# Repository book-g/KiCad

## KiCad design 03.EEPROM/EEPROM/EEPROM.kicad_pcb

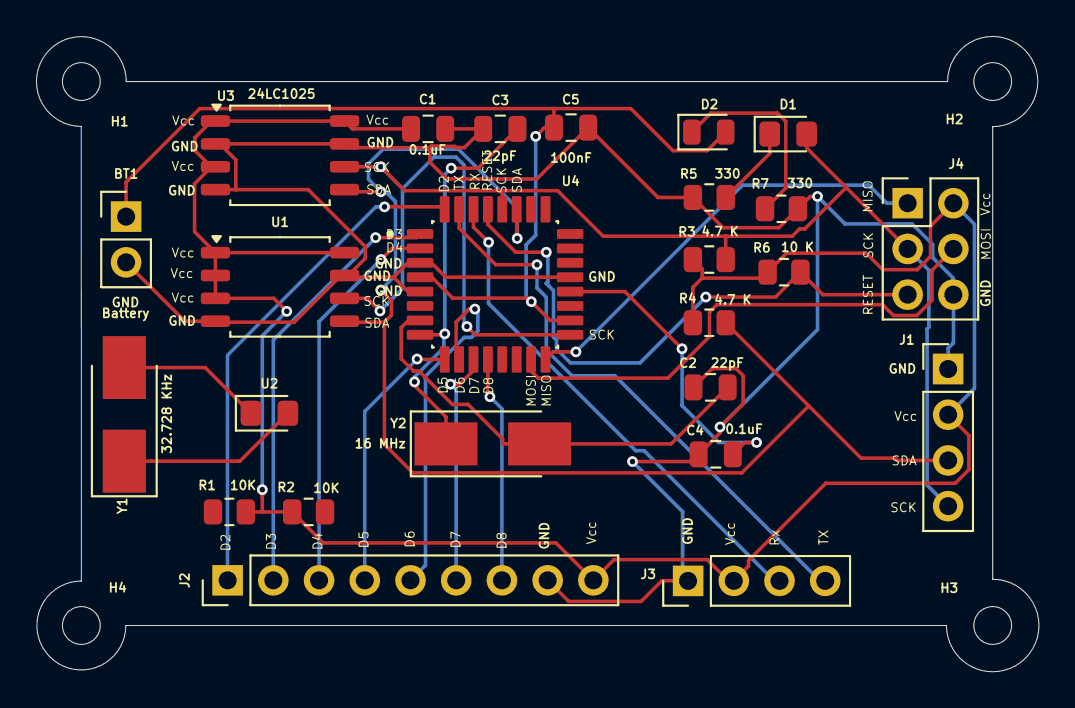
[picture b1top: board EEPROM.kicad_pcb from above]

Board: 2 copper layers, 55.7 x 35.3 mm, 29 parts (0 on the bottom side), 24 nets.

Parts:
BT1: Battery; PinHeader_1x02_P2.54mm_Vertical
C1, C4: 0.1uF; C_0805_2012Metric
C2, C3: 22pF; C_0805_2012Metric
C5: 100nF; C_0805_2012Metric
D1: LED; LED_0805_2012Metric_Pad1.15x1.40mm_HandSolder
D2: LED; LED_0805_2012Metric
H1, H2, H3, H4: MountingHole; MountingHole_2.1mm
J1, J3: Conn_01x04_Pin; PinHeader_1x04_P2.54mm_Vertical
J2: Conn_01x09_Pin; PinHeader_1x09_P2.54mm_Vertical
J4: Conn_02x03_Odd_Even; PinHeader_2x03_P2.54mm_Vertical
R1, R2: 10K; R_0805_2012Metric
R3, R4: 4.7 K; R_0805_2012Metric
R5, R7: 330; R_0805_2012Metric
R6: 10 K; R_0805_2012Metric
U1, U3: 24LC1025; SOIC-8_5.3x5.3mm_P1.27mm
U2: DS1337S_; LED_0805_2012Metric_Pad1.15x1.40mm_HandSolder
U4: ATMEGA328P-AU; QFP80P900X900X120-32N
Y1: 32.728 KHz; Crystal_SMD_5032-2Pin_5.0x3.2mm_HandSoldering
Y2: 16 MHz; Crystal_SMD_5032-2Pin_5.0x3.2mm_HandSoldering

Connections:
/D2: J2.1, U4.32 (PD2)
/D3: J2.2, U4.1 (PD3)
/D4: J2.3, U4.2 (PD4)
/D5: J2.4, U4.9 (PD5)
/D6: J2.5, U4.10 (PD6)
/D7: J2.6, U4.11 (PD7)
/D8: J2.7, U4.12 (PB0)
/MISO: J4.1, U4.16 (PB4)
/MOSI: J4.4, U4.15 (PB3)
/RESET: J4.5, R6.2, U4.29 (PC6/~RESET)
/RX: J3.3, U4.30 (PD0)
/SCK: D1.2 (A), J1.4, J4.3, R3.2, U1.6 (SCL), U3.6 (SCL), U4.17 (PB5), U4.28 (PC5)
/SDA: J1.3, R4.2, U1.5 (SDA), U3.5 (SDA), U4.27 (PC4)
/TX: J3.4, U4.31 (PD1)
/Vcc: C1.1, J1.2, J2.9, J3.2, J4.2, R1.1, R2.1, R3.1, R4.1, R6.1, U1.1 (A0), U1.2 (A1), U1.3 (A2), U1.8 (VCC), U3.1 (A0), U3.3 (A2), U3.8 (VCC)
GND: BT1.2 (-), C1.2, C2.1, C3.1, C4.1, C5.2, J1.1, J2.8, J3.1, J4.6, R5.1, R7.2, U1.4 (GND), U1.7 (WP), U3.2 (A1), U3.4 (GND), U3.7 (WP), U4.3 (GND), U4.5 (GND), U4.21 (GND)
unnamed: BT1.1 (+), C5.1, D2.2 (A), U4.4 (VCC), U4.18 (AVCC)
unnamed: D1.1 (K), R5.2
unnamed: D2.1 (K), R7.1
unnamed: U2.1 (X1), Y1.2
unnamed: U2.2 (X2), Y1.1
unnamed: C4.2, U4.20 (AREF)
unnamed: C2.2, U4.7 (PB6), Y2.2
unnamed: C3.2, U4.8 (PB7), Y2.1

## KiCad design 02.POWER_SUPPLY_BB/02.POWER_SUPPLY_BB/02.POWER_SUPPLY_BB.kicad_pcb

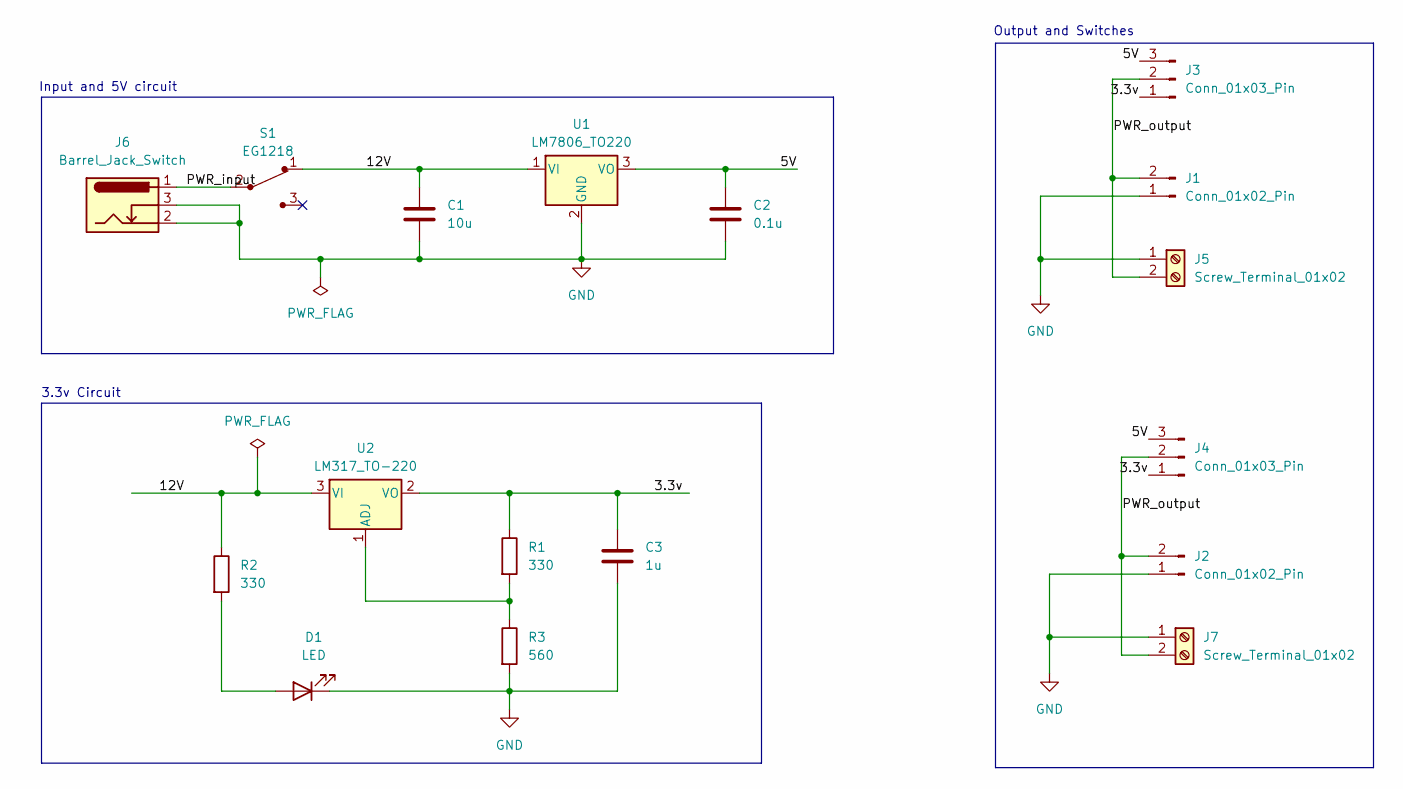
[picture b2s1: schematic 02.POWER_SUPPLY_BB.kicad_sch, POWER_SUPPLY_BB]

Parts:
C1: 10u; C_Disc_D3.0mm_W1.6mm_P2.50mm
C2: 0.1u; C_Disc_D3.0mm_W1.6mm_P2.50mm
C3: 1u; C_Disc_D3.0mm_W1.6mm_P2.50mm
D1: LED; LED_D5.0mm
J1, J2: Conn_01x02_Pin; PinHeader_1x02_P2.54mm_Vertical
J3, J4: Conn_01x03_Pin; PinHeader_1x03_P2.54mm_Vertical
J5, J7: Screw_Terminal_01x02; TerminalBlock_bornier-2_P5.08mm
J6: Barrel_Jack_Switch; BarrelJack_Horizontal
R1, R2: 330; R_Axial_DIN0204_L3.6mm_D1.6mm_P7.62mm_Horizontal
R3: 560; R_Axial_DIN0204_L3.6mm_D1.6mm_P7.62mm_Horizontal
S1: EG1218; Switch_Slide_11.6x4mm_EG1218; MPN EG1218; Digi-Key_PN EG1903-ND
U1: LM7806_TO220; TO-220-3_Vertical
U2: LM317_TO-220; TO-220-3_Vertical

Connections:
/3.3v: C3.1, J3.1, J4.1, R1.1, U2.2 (VO)
/5V: C2.1, J3.3, J4.3, U1.3 (VO)
/12V: C1.1, R2.1, S1.1, U1.1 (VI), U2.3 (VI)
/PWR_input: J6.1, S1.2
/PWR_output: J1.2, J2.2, J3.2, J4.2, J5.2, J7.2
GND: C1.2, C2.2, C3.2, D1.1 (K), J1.1, J2.1, J5.1, J6.2, J6.3, J7.1, R3.2, U1.2 (GND)
unnamed: D1.2 (A), R2.2
unnamed: R1.2, R3.1, U2.1 (ADJ)

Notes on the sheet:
3.3v Circuit
Output and Switches
Input and 5V circuit

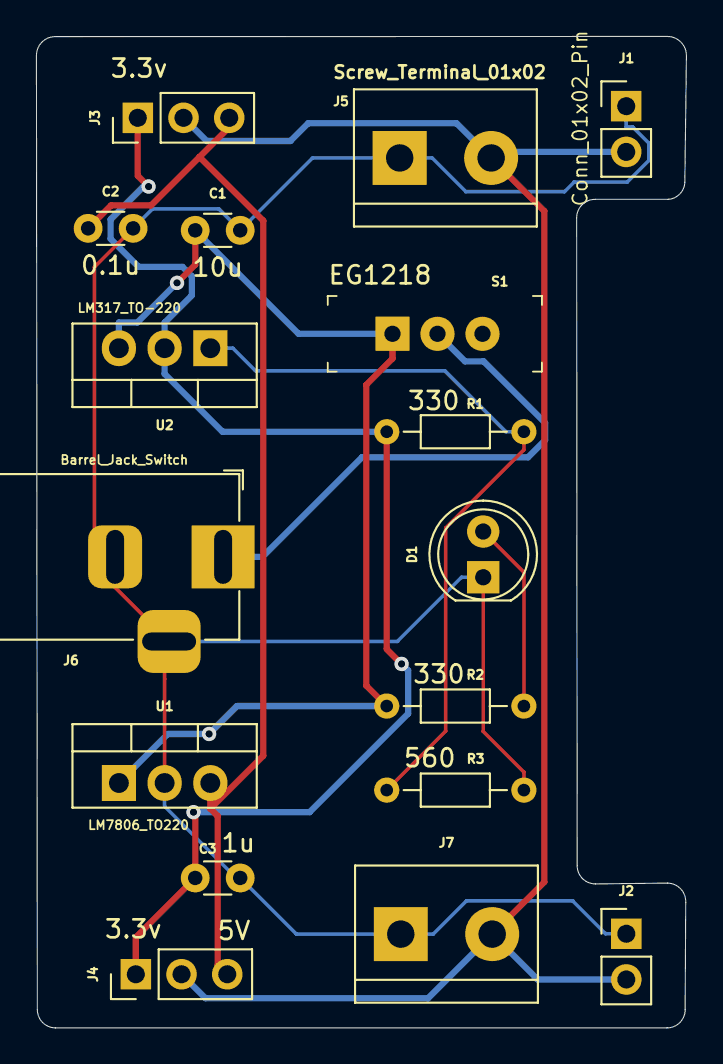
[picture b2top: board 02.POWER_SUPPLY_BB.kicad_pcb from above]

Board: 2 copper layers, 36.1 x 55.1 mm, 17 parts (0 on the bottom side), 8 nets.

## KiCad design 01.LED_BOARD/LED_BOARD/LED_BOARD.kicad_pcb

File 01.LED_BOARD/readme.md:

for auto backup - in window - preference --> preference --> schematic editor -> grid

Fast Grid Switching

Grid 1 :  50.00 mils (1.2700 mm)
Grid 2 :  25.00 mils (0.6350 mm)

Grid Overrides

Connected items : 50.00 mils (1.2700 mm)
Wires           : 12.50 mils (0.3175 mm)
Text            : 50.00 mils (1.2700 mm)
Graphics        : 12.50 mils (0.3175 mm)

Battery:BatteryHolder_Keystone_1058_1x2032

LED_THT:LED_D5.0mm

Resistor_THT:R_Axial_DIN0204_L3.6mm_D1.6mm_P7.62mm_Horizontal

Button_Switch_THT:SW_TH_Tactile_Omron_B3F-10xx

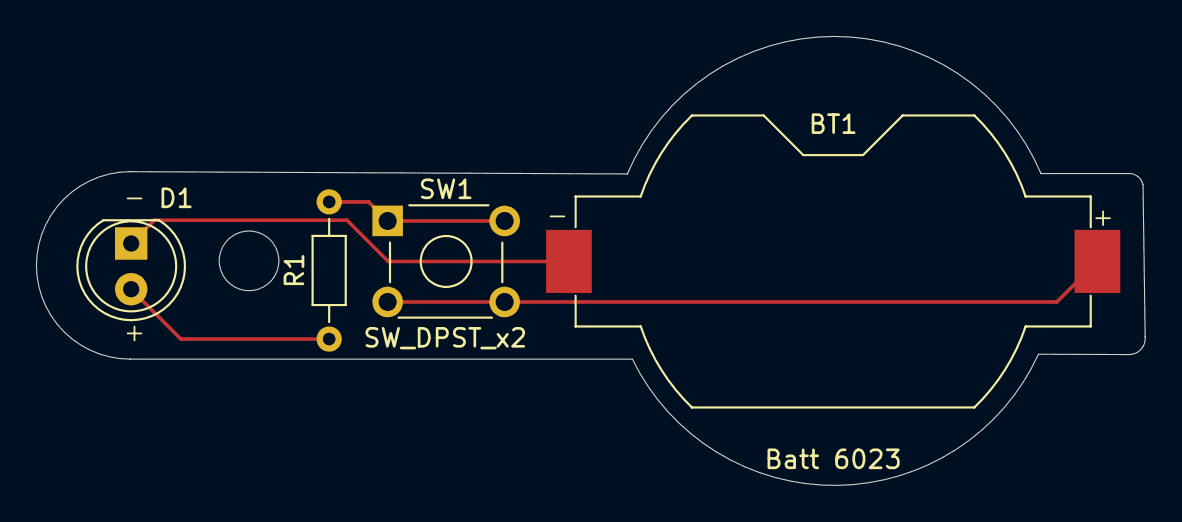
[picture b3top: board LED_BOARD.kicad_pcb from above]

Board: 2 copper layers, 61.6 x 24.9 mm, 4 parts (0 on the bottom side), 4 nets.

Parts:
BT1: Batt 6023; BatteryHolder_Keystone_1058_1x2032
D1: LED; LED_D5.0mm
R1: R; R_Axial_DIN0204_L3.6mm_D1.6mm_P7.62mm_Horizontal
SW1: SW_DPST_x2; SW_TH_Tactile_Omron_B3F-10xx

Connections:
/BAT_POS: BT1.1 (+), SW1.2 (B)
/LED_ANODE: D1.2 (A), R1.1
/LED_CATHODE: BT1.2 (-), D1.1 (K)
unnamed: R1.2, SW1.1 (A)

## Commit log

2025-04-20 LED BOARD - EESCHEMA - SETUP
2025-04-20 LED BOARD - EESCHEMA - SYMBOL
2025-04-20 LED BOARD - EESCHEMA - ARRANGE, ANNOTATE, ASSOCIATE (FOOTPRINT)
2025-04-20 LED BOARD - EESCHEMA - WIRING
2025-04-20 LED BOARD - EESCHEMA - COMMENT
2025-04-20 LED BOARD - PCB - SETUP
2025-04-20 LED BOARD - PCB - OUTLINE AND CONSTRAINTS
2025-04-20 LED BOARD - PCB - ROUTE
2025-04-20 LEDBOARD - PCB - REFINED OUTLINE AND CONSTRAINTS
2025-04-20 LEDBOARD - PCB - SILKSCREEN
2025-04-20 LED BOARD - PCB - SILKSCREEN
2025-04-20 LED BOARD MODEL
2025-04-22 index
2025-04-23 LED BOARD UI changes
2025-04-23 Title changes
2025-04-23 LED BOARD
2025-04-23 POWER_SUPPLY_BB - EESCHEMA - SETUP
2025-04-23 POWER_SUPPLY_BB - EESCHEMA - SYMBOL
2025-04-23 POWER_SUPPLY_BB - EESCHEMA - ARRANGE,ANNOTATE
2025-04-23 POWER_SUPPLY_BB - EESCHEMA - ASSOCIATE
2025-04-23 POWER_SUPPLY_BB - EESCHEMA - WIRING
2025-04-23 POWER_SUPPLY_BB - EESCHEMA - NET
2025-04-23 POWER_SUPPLY_BB - EESCHEMA - COMMENTS
2025-04-23 POWER_SUPPLY_BB - PCB - SETUP
2025-04-23 POWER_SUPPLY_BB - PCB - OUTLINE AND CONSTRAINTS, FOOTPRINTS
2025-04-23 POWER_SUPPLY_BB - PCB - OUTLINE AND CONSTRAINTS, FOOTPRINTS, MODEL
2025-04-23 POWER SUPPLY BB - PCB - CHANGE AUTO ROUTING
2025-04-24 02.POWER_SUPPLY_BB - PCB - SILKSCREEN
2025-04-24 02.POWER_SUPPLY_BB - PCB - DIMENSION
2025-04-24 EEPROM - EESCHEMA - SETUP
2025-04-24 EEPROM - EESCHEMA - SYMBOL
2025-04-24 EEPROM - EESCHEMA - SYMBOL 2 SHEET
2025-04-24 EEPROM - EESCHEMA - ARRANGE, ANNOTATE
2025-04-24 EEPROM - EESCHEMA - EDIT COMPONENT
2025-04-24 EEPROM - EESCHEMA - ASSOCIATE
2025-04-24 EEPROM - EESCHEMA - WIRING 1
2025-04-24 EEPROM - EESCHEMA - WIRING 2
2025-04-24 EEPROM - EESCHEMA - WIRING 3
2025-04-24 EEPROM - EESCHEMA - NETS
2025-04-24 EEPROM - EESCHEMA - COMMENT
2025-04-24 EEPROM - PCB -SETUP
2025-04-24 EEPROM - PCB - ROUTING
2025-04-25 EEPROM - PCB - LAYER 2 COPPER FILL
2025-04-25 4 layer
